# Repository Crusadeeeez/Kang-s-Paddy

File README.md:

# Kang's Paddy
Simplest (1st iteration) Macro Pad, 3 regular keys, 1 rectangular key, and 1 knob for custom/volume control. Literally. Self - Explainatory. But this project hopefully help me gain more insight about electrical and electronic engineering, which im pursuing, and robotics, which im a fan of and dream succeding in.
## Schematics

## PCB

## CAD

### Top

### Bottom

## BOM
 - 1x PCB
 - 1x Seeed XIAO RP2040
 - 4x Cherry MX Key
 - 4x Blank DSA keycaps
 - 1x EC11 Encoder
 - 4x M3x16mm screws

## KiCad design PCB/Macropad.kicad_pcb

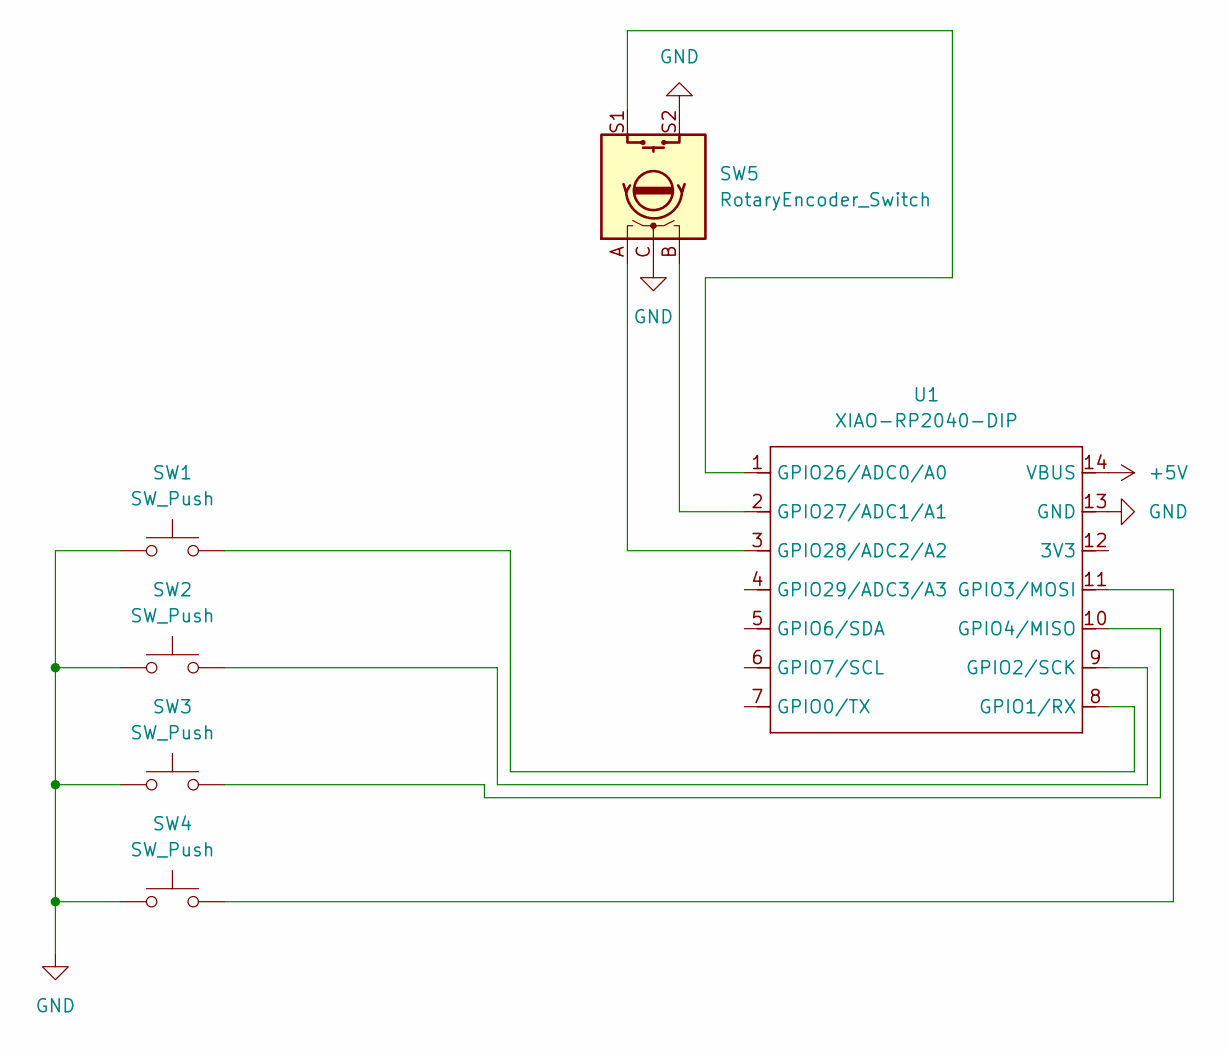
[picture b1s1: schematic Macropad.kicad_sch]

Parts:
SW1, SW2, SW3, SW4: SW_Push; SW_Cherry_MX_1.00u_PCB
SW5: RotaryEncoder_Switch; RotaryEncoder_Alps_EC11E-Switch_Vertical_H20mm
U1: XIAO-RP2040-DIP

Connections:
+5V: U1.14 (VBUS)
GND: SW1.1, SW2.1, SW3.1, SW4.1, SW5.C, SW5.S2, U1.13 (GND)
unnamed: SW1.2, U1.8 (GPIO1/RX)
unnamed: SW2.2, U1.9 (GPIO2/SCK)
unnamed: SW4.2, U1.11 (GPIO3/MOSI)
unnamed: SW3.2, U1.10 (GPIO4/MISO)
unnamed: SW5.S1, U1.1 (GPIO26/ADC0/A0)
unnamed: SW5.B, U1.2 (GPIO27/ADC1/A1)
unnamed: SW5.A, U1.3 (GPIO28/ADC2/A2)

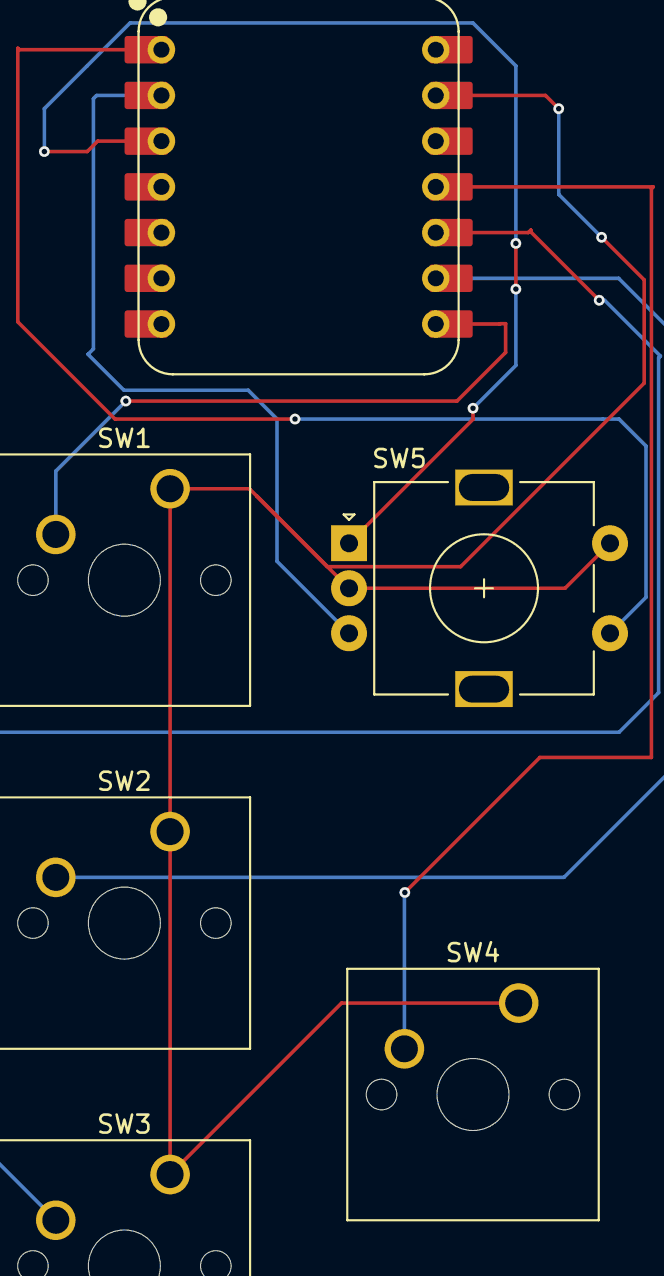
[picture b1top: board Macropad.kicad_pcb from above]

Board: 2 copper layers, 6 parts (0 on the bottom side), 8 nets.

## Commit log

2025-12-27 Create PCB
2025-12-27 Create tml
